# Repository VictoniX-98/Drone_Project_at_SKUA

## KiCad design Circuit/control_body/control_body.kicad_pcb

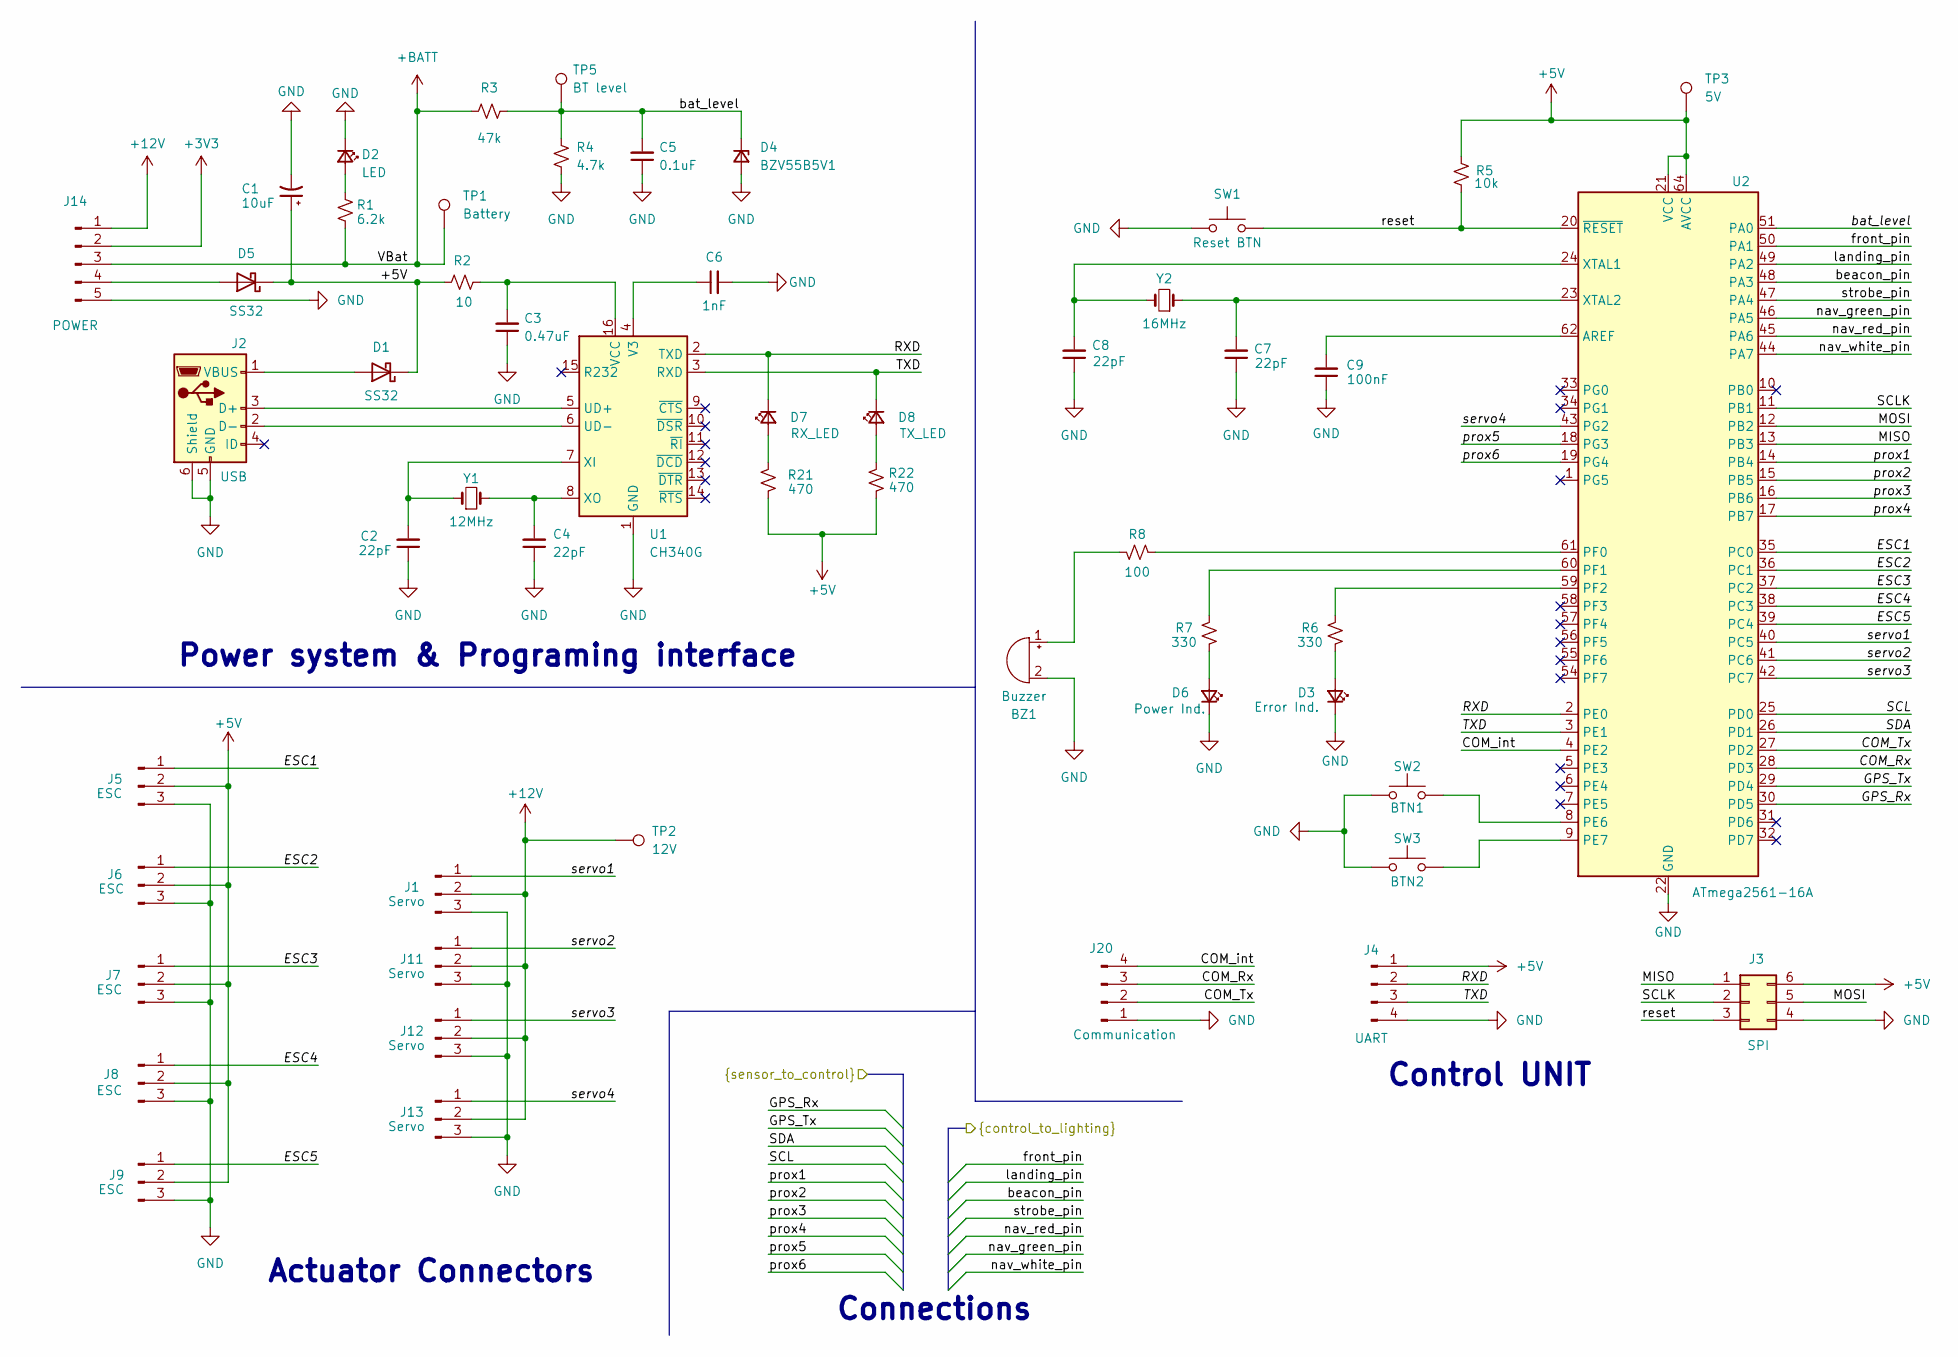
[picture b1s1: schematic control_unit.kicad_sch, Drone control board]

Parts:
BZ1: Buzzer; Buzzer_TDK_PS1240P02BT_D12.2mm_H6.5mm
C1: 10uF; CP_Elec_4x3
C2, C4, C7, C8: 22pF; C_0805_2012Metric_Pad1.18x1.45mm_HandSolder
C3: 0.47uF; C_0805_2012Metric_Pad1.18x1.45mm_HandSolder
C5: 0.1uF; C_0805_2012Metric_Pad1.18x1.45mm_HandSolder
C6: 1nF; C_0805_2012Metric_Pad1.18x1.45mm_HandSolder
C9: 100nF; C_0805_2012Metric_Pad1.18x1.45mm_HandSolder
D1, D5: SS32; D_SMA
D2: LED; LED_1206_3216Metric
D3: Error Ind.; LED_1206_3216Metric
D4: BZV55B5V1; D_MiniMELF
D6: Power Ind.; LED_1206_3216Metric
D7: RX_LED; LED_1206_3216Metric
D8: TX_LED; LED_1206_3216Metric
J1, J11, J12, J13: Servo; Wuerth_WR-WTB_64800311622_1x03_P1.50mm_Vertical
J2: USB; USB_Micro-B_Amphenol_10118194_Horizontal
J3: SPI; PinHeader_2x03_P2.54mm_Vertical
J4: UART; PinHeader_1x04_P2.54mm_Vertical
J5, J6, J7, J8, J9: ESC; Wuerth_WR-WTB_64800311622_1x03_P1.50mm_Vertical
J14: POWER; JST_PH_B5B-PH-K_1x05_P2.00mm_Vertical
J20: Communication; Wuerth_WR-WTB_64800411622_1x04_P1.50mm_Vertical
R1: 6.2k; R_0805_2012Metric_Pad1.20x1.40mm_HandSolder
R2: 10; R_0805_2012Metric_Pad1.20x1.40mm_HandSolder
R3: 47k; R_0805_2012Metric_Pad1.20x1.40mm_HandSolder
R4: 4.7k; R_0805_2012Metric_Pad1.20x1.40mm_HandSolder
R5: 10k; R_0805_2012Metric_Pad1.20x1.40mm_HandSolder
R6, R7: 330; R_0805_2012Metric_Pad1.20x1.40mm_HandSolder
R8: 100; R_0805_2012Metric_Pad1.20x1.40mm_HandSolder
R21, R22: 470; R_0805_2012Metric_Pad1.20x1.40mm_HandSolder
SW1: Reset BTN; SW_SPST_CK_RS282G05A3
SW2: BTN1; SW_SPST_B3U-1000P
SW3: BTN2; SW_SPST_B3U-1000P
TP1: Battery; TestPoint_Pad_D2.0mm
TP2: 12V; TestPoint_Pad_D2.0mm
TP3: 5V; TestPoint_Pad_D2.0mm
TP5: BT level; TestPoint_Pad_D2.0mm
U1: CH340G; SOIC-16_3.9x9.9mm_P1.27mm
U2: ATmega2561-16A; TQFP-64_14x14mm_P0.8mm
Y1: 12MHz; Crystal_SMD_HC49-SD
Y2: 16MHz; Crystal_SMD_HC49-SD

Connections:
+3V3: J14.2; also elsewhere on the board
+5V: BZ1.2 (-), C1.1, C1.2, C2.1, C3.1, C4.1, C5.1, C6.2, C7.1, C8.1, C9.1, D1.1 (K), D2.1 (K), D3.1 (K), D4.2 (A), D5.1 (K), D6.1 (K), J1.3, J2.5 (GND), J2.6 (Shield), J3.4, J3.6, J4.1, J4.4, J5.2, J5.3, J6.2, J6.3, J7.2, J7.3, J8.2, J8.3, J9.2, J9.3, J11.3, J12.3, J13.3, J14.5, J20.1, R2.1, R4.2, R5.1, R21.2, R22.2, SW1.1, SW2.2, SW3.2, TP3.1, U1.1 (GND), U2.21 (VCC), U2.22 (GND), U2.52 (VCC), U2.53 (GND), U2.63 (GND), U2.64 (AVCC); also elsewhere on the board
+12V: J1.2, J11.2, J12.2, J13.2, J14.1, TP2.1; also elsewhere on the board
+BATT: J14.3, R1.2, R3.1, TP1.1; also elsewhere on the board
/Control UNIT/COM_Rx: J20.3, U2.28 (PD3)
/Control UNIT/COM_Tx: J20.2, U2.27 (PD2)
/Control UNIT/COM_int: J20.4, U2.4 (PE2)
/Control UNIT/ESC1: J5.1, U2.35 (PC0)
/Control UNIT/ESC2: J6.1, U2.36 (PC1)
/Control UNIT/ESC3: J7.1, U2.37 (PC2)
/Control UNIT/ESC4: J8.1, U2.38 (PC3)
/Control UNIT/ESC5: J9.1, U2.39 (PC4)
/Control UNIT/GPS_Rx: U2.30 (PD5); also elsewhere on the board
/Control UNIT/GPS_Tx: U2.29 (PD4); also elsewhere on the board
/Control UNIT/MISO: J3.1, U2.13 (PB3)
/Control UNIT/MOSI: J3.5, U2.12 (PB2)
/Control UNIT/RXD: D7.1 (K), J4.2, U1.2 (TXD), U2.2 (PE0)
/Control UNIT/SCL: U2.25 (PD0); also elsewhere on the board
/Control UNIT/SCLK: J3.2, U2.11 (PB1)
/Control UNIT/SDA: U2.26 (PD1); also elsewhere on the board
/Control UNIT/TXD: D8.1 (K), J4.3, U1.3 (RXD), U2.3 (PE1)
/Control UNIT/bat_level: C5.2, D4.1 (K), R3.2, R4.1, TP5.1, U2.51 (PA0)
/Control UNIT/beacon_pin: U2.48 (PA3); also elsewhere on the board
/Control UNIT/front_pin: U2.50 (PA1); also elsewhere on the board
/Control UNIT/landing_pin: U2.49 (PA2); also elsewhere on the board
/Control UNIT/nav_green_pin: U2.46 (PA5); also elsewhere on the board
/Control UNIT/nav_red_pin: U2.45 (PA6); also elsewhere on the board
/Control UNIT/nav_white_pin: U2.44 (PA7); also elsewhere on the board
/Control UNIT/prox1: U2.14 (PB4); also elsewhere on the board
/Control UNIT/prox2: U2.15 (PB5); also elsewhere on the board
/Control UNIT/prox3: U2.16 (PB6); also elsewhere on the board
/Control UNIT/prox4: U2.17 (PB7); also elsewhere on the board
/Control UNIT/prox5: U2.18 (PG3); also elsewhere on the board
/Control UNIT/prox6: U2.19 (PG4); also elsewhere on the board
/Control UNIT/reset: J3.3, R5.2, SW1.2, U2.20 (~RESET)
/Control UNIT/servo1: J1.1, U2.40 (PC5)
/Control UNIT/servo2: J11.1, U2.41 (PC6)
/Control UNIT/servo3: J12.1, U2.42 (PC7)
/Control UNIT/servo4: J13.1, U2.43 (PG2)
/Control UNIT/strobe_pin: U2.47 (PA4); also elsewhere on the board
unnamed: BZ1.1 (+), R8.2
unnamed: D1.2 (A), J2.1 (VBUS)
unnamed: D2.2 (A), R1.1
unnamed: D3.2 (A), R6.1
unnamed: D5.2 (A), J14.4
unnamed: D6.2 (A), R7.1
unnamed: D7.2 (A), R21.1
unnamed: D8.2 (A), R22.1
unnamed: J2.3 (D+), U1.5 (UD+)
unnamed: J2.2 (D-), U1.6 (UD-)
unnamed: C6.1, U1.4 (V3)
unnamed: C3.2, R2.2, U1.16 (VCC)
unnamed: C2.2, U1.7 (XI), Y1.1
unnamed: C4.2, U1.8 (XO), Y1.2
unnamed: C9.2, U2.62 (AREF)
unnamed: SW2.1, U2.8 (PE6)
unnamed: SW3.1, U2.9 (PE7)
unnamed: R8.1, U2.61 (PF0)
unnamed: R7.2, U2.60 (PF1)
unnamed: R6.2, U2.59 (PF2)
unnamed: C8.2, U2.24 (XTAL1), Y2.2
unnamed: C7.2, U2.23 (XTAL2), Y2.1

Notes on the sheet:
Control UNIT
Connections
Power system & Programing interface
Actuator Connectors

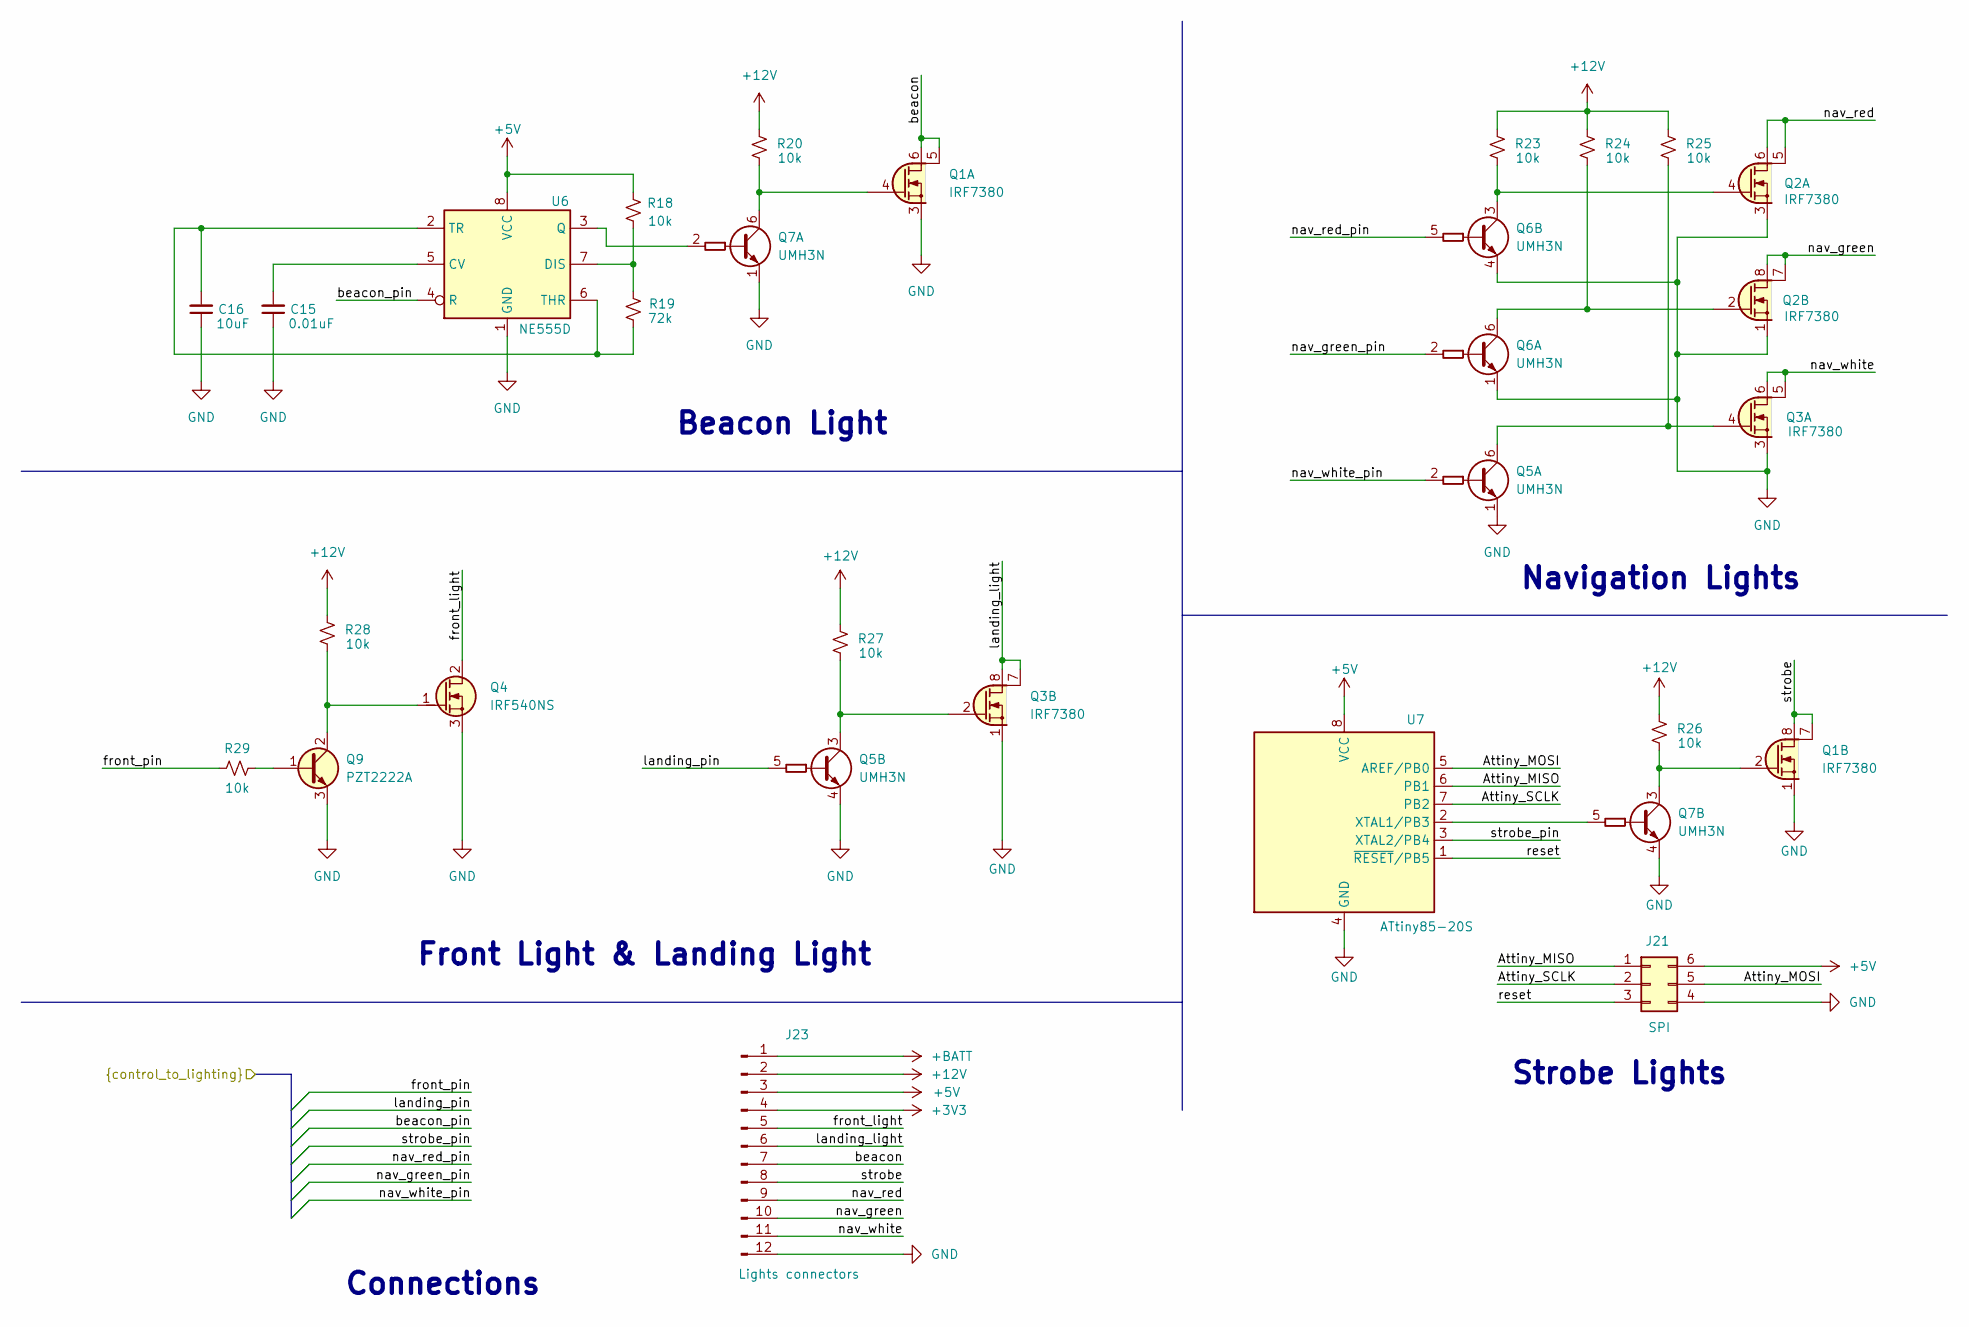
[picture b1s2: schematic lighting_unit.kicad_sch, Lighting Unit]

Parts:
C15: 0.01uF; C_0805_2012Metric_Pad1.18x1.45mm_HandSolder
C16: 10uF; C_0805_2012Metric_Pad1.18x1.45mm_HandSolder
J21: SPI; PinHeader_2x03_P2.54mm_Vertical
J23: Lights connectors; PinHeader_2x06_P2.54mm_Horizontal
Q1, Q2, Q3: IRF7380; SO-8_3.9x4.9mm_P1.27mm
Q4: IRF540NS; TO-263-2
Q5, Q6, Q7: UMH3N; SOT-363_SC-70-6
Q9: PZT2222A; SOT-223-3_TabPin2
R18, R20, R23, R24, R25, R26, R27, R28, R29: 10k; R_0805_2012Metric_Pad1.20x1.40mm_HandSolder
R19: 72k; R_0805_2012Metric_Pad1.20x1.40mm_HandSolder
U6: NE555D; SOIC-8_3.9x4.9mm_P1.27mm
U7: ATtiny85-20S; SOIC-8W_5.3x5.3mm_P1.27mm

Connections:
+3V3: J23.4; also elsewhere on the board
+5V: C15.1, C16.1, J21.4, J21.6, J23.3, J23.12, Q1.1 (S2), Q1.3 (S1), Q2.1 (S2), Q2.3 (S1), Q3.1 (S2), Q3.3 (S1), Q4.3 (S), Q5.1 (E1), Q5.4 (E2), Q6.1 (E1), Q6.4 (E2), Q7.1 (E1), Q7.4 (E2), Q9.3 (E), R18.2, U6.1 (GND), U6.8 (VCC), U7.4 (GND), U7.8 (VCC); also elsewhere on the board
+12V: J23.2, R20.2, R23.2, R24.2, R25.2, R26.2, R27.2, R28.2; also elsewhere on the board
+BATT: J23.1; also elsewhere on the board
/Control UNIT/beacon_pin: U6.4 (R); also elsewhere on the board
/Control UNIT/front_pin: R29.2; also elsewhere on the board
/Control UNIT/landing_pin: Q5.5 (B2); also elsewhere on the board
/Control UNIT/nav_green_pin: Q6.2 (B1); also elsewhere on the board
/Control UNIT/nav_red_pin: Q6.5 (B2); also elsewhere on the board
/Control UNIT/nav_white_pin: Q5.2 (B1); also elsewhere on the board
/Control UNIT/strobe_pin: U7.3 (XTAL2/PB4); also elsewhere on the board
/Lighting UNIT/Attiny_MISO: J21.1, U7.6 (PB1)
/Lighting UNIT/Attiny_MOSI: J21.5, U7.5 (AREF/PB0)
/Lighting UNIT/Attiny_SCLK: J21.2, U7.7 (PB2)
/Lighting UNIT/beacon: J23.7, Q1.5 (D1), Q1.6 (D1)
/Lighting UNIT/front_light: J23.5, Q4.2 (D)
/Lighting UNIT/landing_light: J23.6, Q3.7 (D2), Q3.8 (D2)
/Lighting UNIT/nav_green: J23.10, Q2.7 (D2), Q2.8 (D2)
/Lighting UNIT/nav_red: J23.9, Q2.5 (D1), Q2.6 (D1)
/Lighting UNIT/nav_white: J23.11, Q3.5 (D1), Q3.6 (D1)
/Lighting UNIT/reset: J21.3, U7.1 (~RESET/PB5)
/Lighting UNIT/strobe: J23.8, Q1.7 (D2), Q1.8 (D2)
unnamed: Q1.4 (G1), Q7.6 (C1), R20.1
unnamed: Q1.2 (G2), Q7.3 (C2), R26.1
unnamed: Q2.4 (G1), Q6.3 (C2), R23.1
unnamed: Q2.2 (G2), Q6.6 (C1), R24.1
unnamed: Q3.4 (G1), Q5.6 (C1), R25.1
unnamed: Q3.2 (G2), Q5.3 (C2), R27.1
unnamed: Q4.1 (G), Q9.2 (C), R28.1
unnamed: Q7.2 (B1), U6.3 (Q)
unnamed: Q7.5 (B2), U7.2 (XTAL1/PB3)
unnamed: Q9.1 (B), R29.1
unnamed: C15.2, U6.5 (CV)
unnamed: R18.1, R19.2, U6.7 (DIS)
unnamed: C16.2, R19.1, U6.2 (TR), U6.6 (THR)

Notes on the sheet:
Navigation Lights
Beacon Light
Front Light & Landing Light
Connections
Strobe Lights

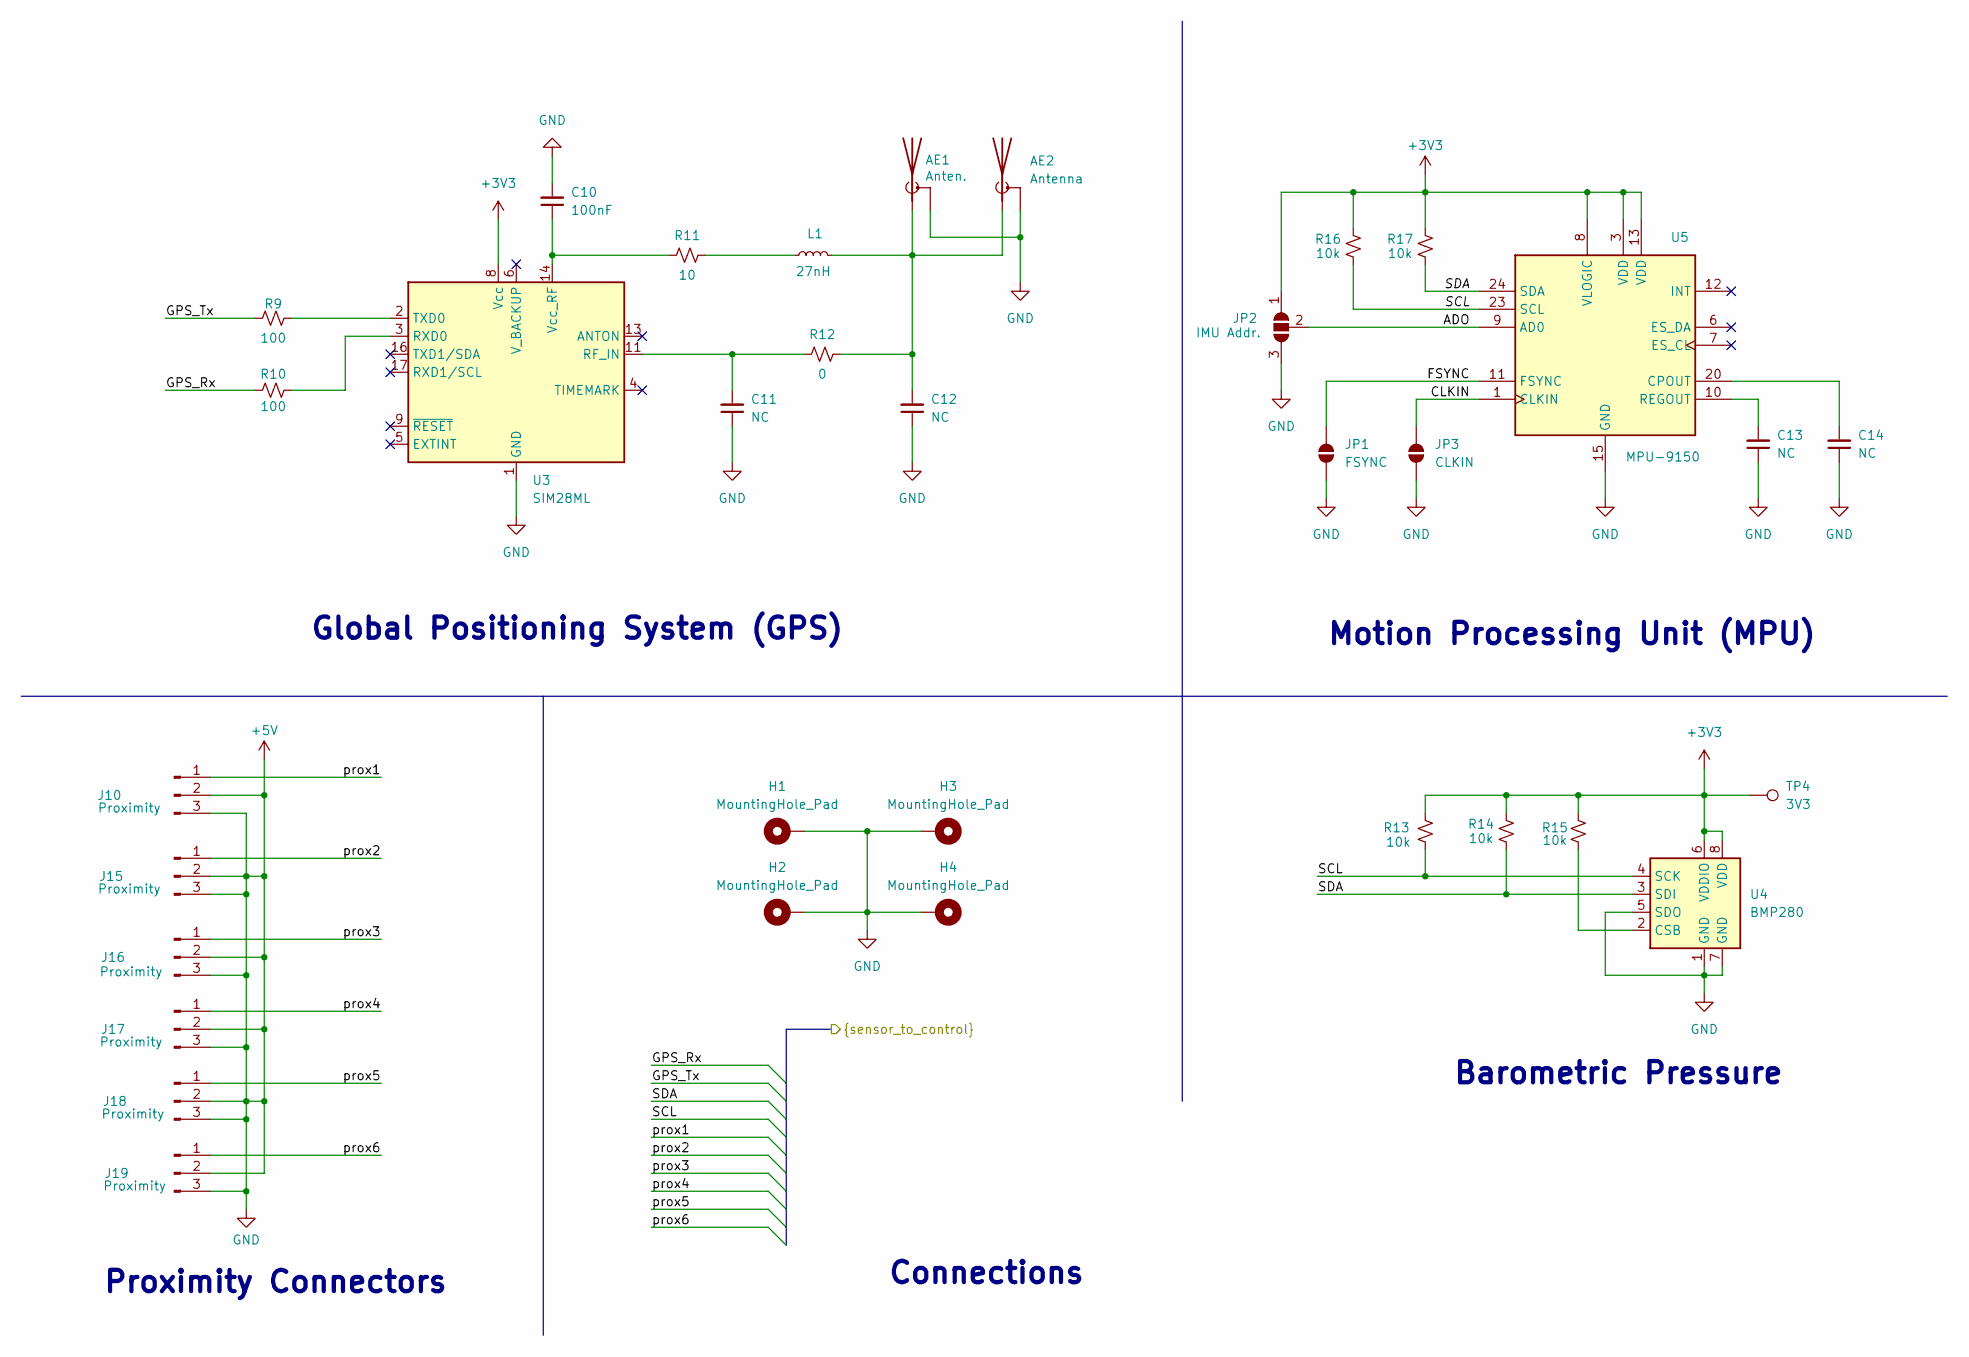
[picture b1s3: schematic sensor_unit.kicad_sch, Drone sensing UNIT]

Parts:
AE1: Anten.; U.FL_Hirose_U.FL-R-SMT-1_Vertical
AE2: Antenna; MMCX_Molex_73415-1471_Vertical
C10: 100nF; C_0805_2012Metric_Pad1.18x1.45mm_HandSolder
C11, C12, C13, C14: NC; C_0805_2012Metric_Pad1.18x1.45mm_HandSolder
H1, H2, H3, H4: MountingHole_Pad; MountingHole_2.2mm_M2_Pad_Via
J10, J15, J16, J17, J18, J19: Proximity; Wuerth_WR-WTB_64800311622_1x03_P1.50mm_Vertical
JP1: FSYNC; SolderJumper-2_P1.3mm_Open_RoundedPad1.0x1.5mm
JP2: IMU Addr.; SolderJumper-3_P1.3mm_Open_RoundedPad1.0x1.5mm
JP3: CLKIN; SolderJumper-2_P1.3mm_Open_RoundedPad1.0x1.5mm
L1: 27nH; L_0805_2012Metric_Pad1.05x1.20mm_HandSolder
R9, R10: 100; R_0805_2012Metric_Pad1.20x1.40mm_HandSolder
R11: 10; R_0805_2012Metric_Pad1.20x1.40mm_HandSolder
R12: 0; R_0805_2012Metric_Pad1.20x1.40mm_HandSolder
R13, R14, R15, R16, R17: 10k; R_0805_2012Metric_Pad1.20x1.40mm_HandSolder
TP4: 3V3; TestPoint_Pad_D2.0mm
U3: SIM28ML
U4: BMP280; Bosch_LGA-8_2x2.5mm_P0.65mm_ClockwisePinNumbering
U5: MPU-9150; InvenSense_QFN-24_4x4mm_P0.5mm

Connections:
+3V3: JP2.1 (A), R13.2, R14.2, R15.2, R16.2, R17.2, TP4.1, U3.8 (Vcc), U4.6 (VDDIO), U4.8 (VDD), U5.3 (VDD), U5.8 (VLOGIC), U5.13 (VDD); also elsewhere on the board
+5V: AE1.2 (Shield), AE2.2 (Shield), C10.2, C11.1, C12.1, C13.1, C14.1, H1.1, H2.1, H3.1, H4.1, J10.2, J10.3, J15.2, J15.3, J16.2, J16.3, J17.2, J17.3, J18.2, J18.3, J19.2, J19.3, JP1.1 (A), JP2.3 (B), JP3.1 (A), U3.1 (GND), U3.10 (GND), U3.12 (GND), U4.1 (GND), U4.5 (SDO), U4.7 (GND), U5.15 (GND), U5.17 (GND), U5.18 (GND); also elsewhere on the board
/Control UNIT/GPS_Rx: R10.1; also elsewhere on the board
/Control UNIT/GPS_Tx: R9.1; also elsewhere on the board
/Control UNIT/SCL: R13.1, R16.1, U4.4 (SCK), U5.23 (SCL); also elsewhere on the board
/Control UNIT/SDA: R14.1, R17.1, U4.3 (SDI), U5.24 (SDA); also elsewhere on the board
/Control UNIT/prox1: J10.1; also elsewhere on the board
/Control UNIT/prox2: J15.1; also elsewhere on the board
/Control UNIT/prox3: J16.1; also elsewhere on the board
/Control UNIT/prox4: J17.1; also elsewhere on the board
/Control UNIT/prox5: J18.1; also elsewhere on the board
/Control UNIT/prox6: J19.1; also elsewhere on the board
/Sensor UNIT/ADO: JP2.2 (C), U5.9 (AD0)
/Sensor UNIT/CLKIN: JP3.2 (B), U5.1 (CLKIN)
/Sensor UNIT/FSYNC: JP1.2 (B), U5.11 (FSYNC)
unnamed: AE1.1 (A), AE2.1 (A), C12.2, L1.2, R12.2
unnamed: L1.1, R11.2
unnamed: C11.2, R12.1, U3.11 (RF_IN)
unnamed: R10.2, U3.3 (RXD0)
unnamed: R9.2, U3.2 (TXD0)
unnamed: C10.1, R11.1, U3.14 (Vcc_RF)
unnamed: R15.1, U4.2 (CSB)
unnamed: C14.2, U5.20 (CPOUT)
unnamed: C13.2, U5.10 (REGOUT)

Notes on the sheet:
Motion Processing Unit (MPU)
Global Positioning System (GPS)
Barometric Pressure
Connections
Proximity Connectors

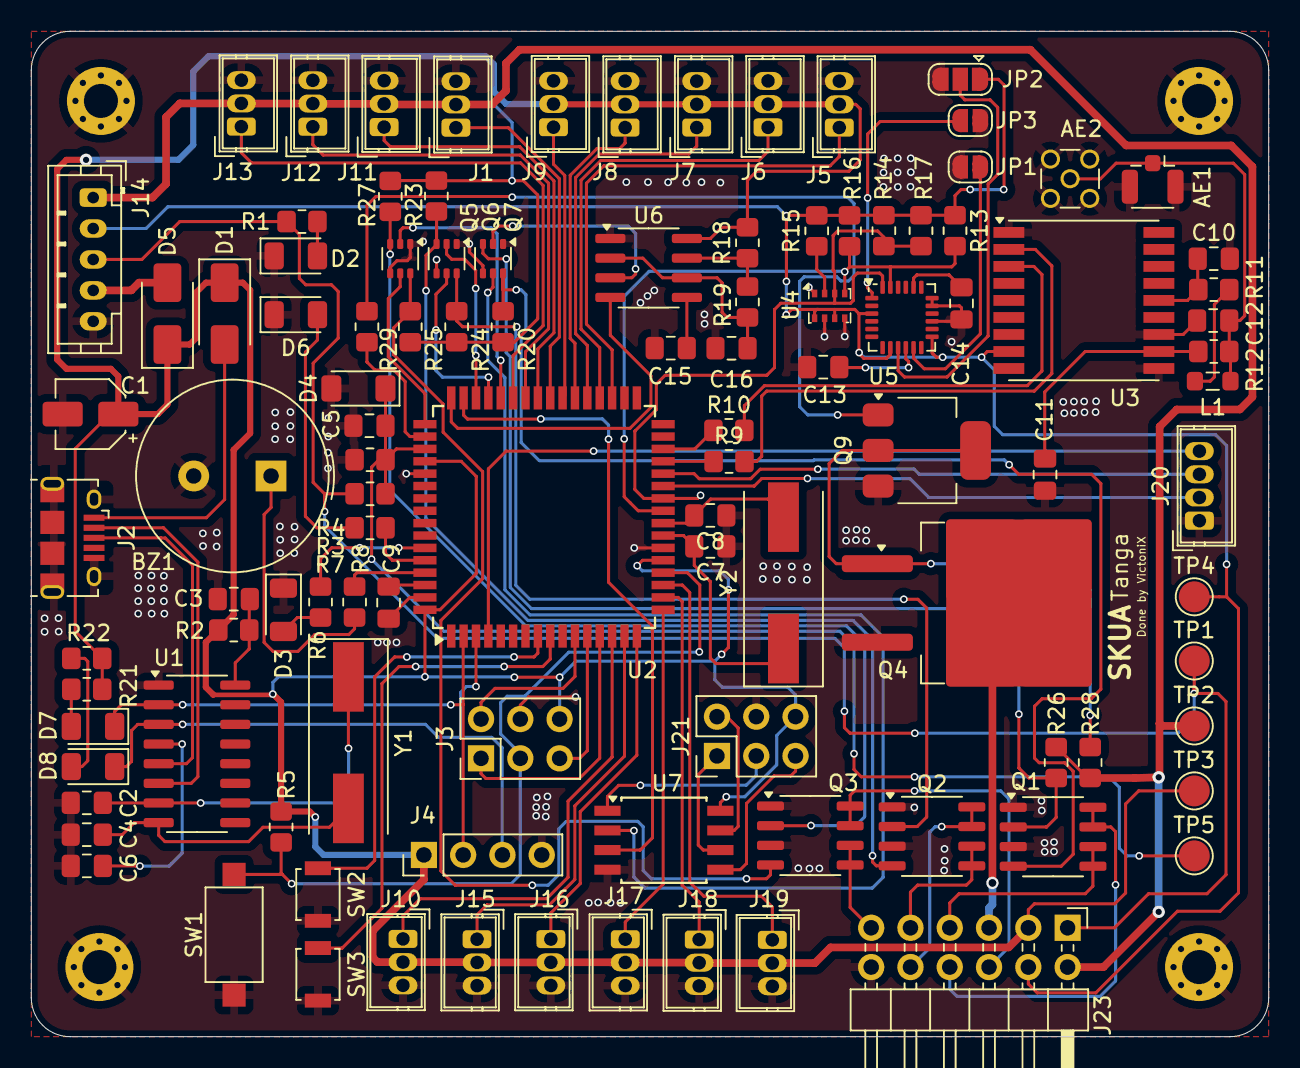
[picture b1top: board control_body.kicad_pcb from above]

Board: 2 copper layers, 80.0 x 65.0 mm, 111 parts (0 on the bottom side), 98 nets.

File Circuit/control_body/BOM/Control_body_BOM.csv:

Designator,Footprint,Comment
AE1,Connector_Coaxial:U.FL_Hirose_U.FL-R-SMT-1_Vertical,Anten.
AE2,Connector_Coaxial:MMCX_Molex_73415-1471_Vertical,Antenna
BZ1,Buzzer_Beeper:Buzzer_TDK_PS1240P02BT_D12.2mm_H6.5mm,Buzzer
"C1,C16",-- mixed values --,10uF
"C2,C4,C7,C8",Capacitor_SMD:C_0805_2012Metric_Pad1.18x1.45mm_HandSolder,22pF
C3,Capacitor_SMD:C_0805_2012Metric_Pad1.18x1.45mm_HandSolder,0.47uF
C5,Capacitor_SMD:C_0805_2012Metric_Pad1.18x1.45mm_HandSolder,0.1uF
C6,Capacitor_SMD:C_0805_2012Metric_Pad1.18x1.45mm_HandSolder,1nF
"C9,C10",Capacitor_SMD:C_0805_2012Metric_Pad1.18x1.45mm_HandSolder,100nF
"C11,C12,C13,C14",Capacitor_SMD:C_0805_2012Metric_Pad1.18x1.45mm_HandSolder,NC
C15,Capacitor_SMD:C_0805_2012Metric_Pad1.18x1.45mm_HandSolder,0.01uF
"D1,D5",Diode_SMD:D_SMA,SS32
D2,LED_SMD:LED_1206_3216Metric,LED
D3,LED_SMD:LED_1206_3216Metric,Error Ind.
D4,Diode_SMD:D_MiniMELF,BZV55B5V1
D6,LED_SMD:LED_1206_3216Metric,Power Ind.
D7,LED_SMD:LED_1206_3216Metric,RX_LED
D8,LED_SMD:LED_1206_3216Metric,TX_LED
"J1,J11,J12,J13",Connector_Wuerth:Wuerth_WR-WTB_64800311622_1x03_P1.50mm_Vertical,Servo
J2,Connector_USB:USB_Micro-B_Molex_47346-0001,USB
"J3,J21",Connector_PinHeader_2.54mm:PinHeader_2x03_P2.54mm_Vertical,SPI
J4,Connector_PinHeader_2.54mm:PinHeader_1x04_P2.54mm_Vertical,UART
"J5,J6,J7,J8,J9",Connector_Wuerth:Wuerth_WR-WTB_64800311622_1x03_P1.50mm_Vertical,ESC
"J10,J15,J16,J17,J18,J19",Connector_Wuerth:Wuerth_WR-WTB_64800311622_1x03_P1.50mm_Vertical,Proximity
J14,Connector_JST:JST_PH_B5B-PH-K_1x05_P2.00mm_Vertical,POWER
J20,Connector_Wuerth:Wuerth_WR-WTB_64800411622_1x04_P1.50mm_Vertical,Communication
J23,Connector_PinHeader_2.54mm:PinHeader_2x06_P2.54mm_Horizontal,Lights connectors
L1,Inductor_SMD:L_0805_2012Metric_Pad1.05x1.20mm_HandSolder,27nH
"Q1,Q2,Q3",Package_SO:SO-8_3.9x4.9mm_P1.27mm,IRF7380
Q4,Package_TO_SOT_SMD:TO-263-2,IRF540NS
"Q5,Q6,Q7",Package_TO_SOT_SMD:SOT-363_SC-70-6,UMH3N
Q9,Package_TO_SOT_SMD:SOT-223-3_TabPin2,PZT2222A
R1,Resistor_SMD:R_0805_2012Metric_Pad1.20x1.40mm_HandSolder,6.2k
R3,Resistor_SMD:R_0805_2012Metric_Pad1.20x1.40mm_HandSolder,47k
R4,Resistor_SMD:R_0805_2012Metric_Pad1.20x1.40mm_HandSolder,4.7k
"R2,R11",Resistor_SMD:R_0805_2012Metric_Pad1.20x1.40mm_HandSolder,10
"R5,R13,R14,R15,R16,R17,R18,R20,R23,R24,R25,R26,R27,R28,R29",Resistor_SMD:R_0805_2012Metric_Pad1.20x1.40mm_HandSolder,10k
"R6,R7",Resistor_SMD:R_0805_2012Metric_Pad1.20x1.40mm_HandSolder,330
"R8,R9,R10",Resistor_SMD:R_0805_2012Metric_Pad1.20x1.40mm_HandSolder,100
R12,Resistor_SMD:R_0805_2012Metric_Pad1.20x1.40mm_HandSolder,0
R19,Resistor_SMD:R_0805_2012Metric_Pad1.20x1.40mm_HandSolder,72k
"R21,R22",Resistor_SMD:R_0805_2012Metric_Pad1.20x1.40mm_HandSolder,470
SW1,Button_Switch_SMD:SW_SPST_CK_RS282G05A3,Reset BTN
SW2,Button_Switch_SMD:SW_SPST_B3U-1000P,BTN1
SW3,Button_Switch_SMD:SW_SPST_B3U-1000P,BTN2
U1,Package_SO:SOIC-16_3.9x9.9mm_P1.27mm,CH340G
U2,Package_QFP:TQFP-64_14x14mm_P0.8mm,ATmega2561-16A
U3,RF_GPS:SIM28ML,SIM28ML
U4,Package_LGA:Bosch_LGA-8_2x2.5mm_P0.65mm_ClockwisePinNumbering,BMP280
U5,Sensor_Motion:InvenSense_QFN-24_4x4mm_P0.5mm,MPU-9150
U6,Package_SO:SOIC-8_3.9x4.9mm_P1.27mm,NE555D
U7,Package_SO:SOIC-8W_5.3x5.3mm_P1.27mm,ATtiny85-20S
Y1,Crystal:Crystal_SMD_HC49-SD,12MHz
Y2,Crystal:Crystal_SMD_HC49-SD,16MHz

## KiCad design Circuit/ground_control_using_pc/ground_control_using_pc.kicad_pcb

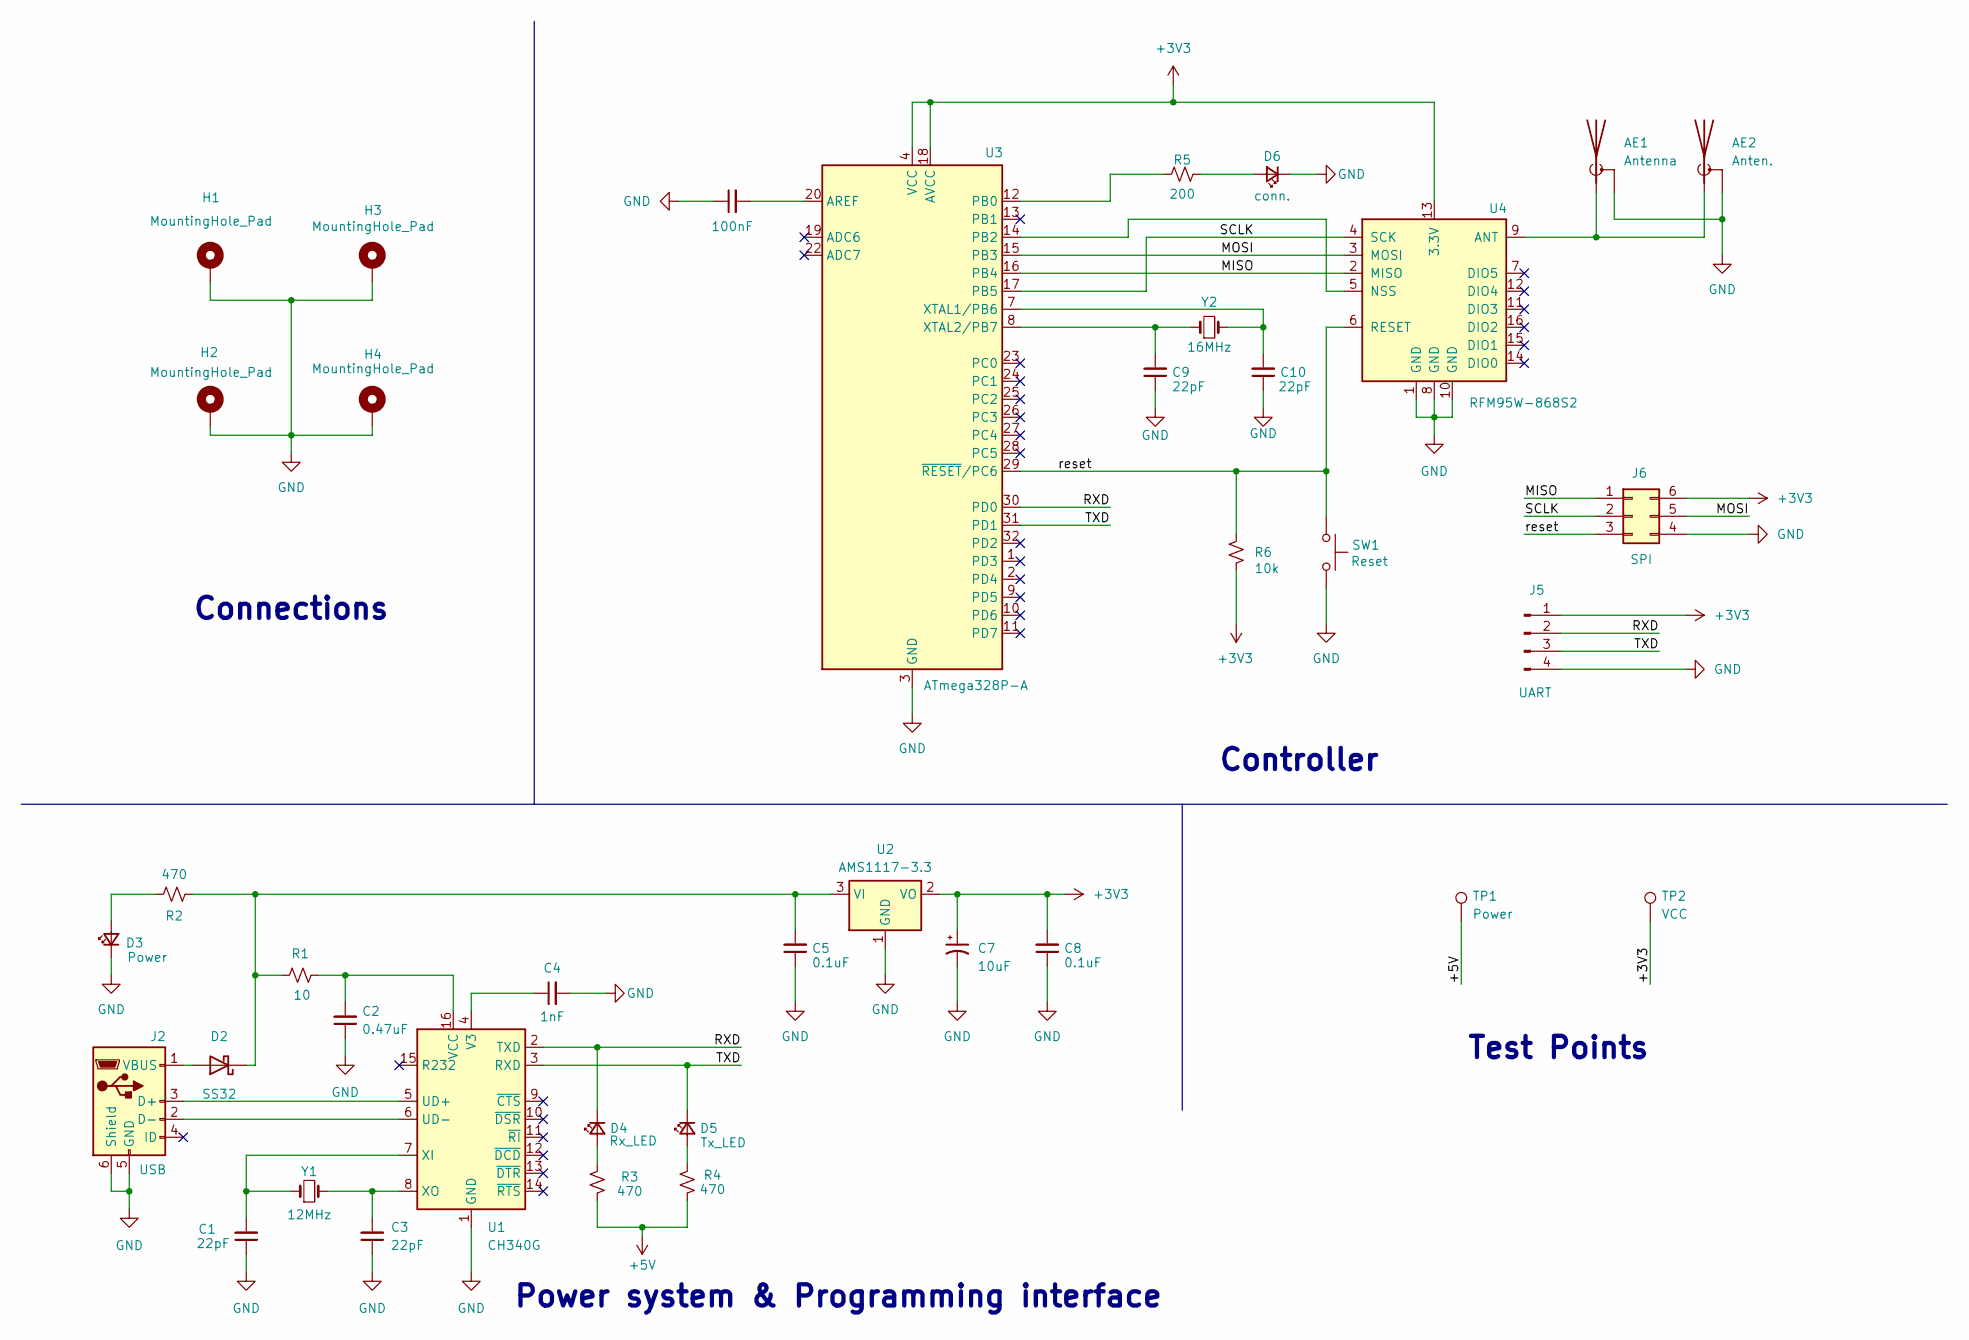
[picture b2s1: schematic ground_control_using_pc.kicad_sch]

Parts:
AE1: Antenna; MMCX_Molex_73415-1471_Vertical
AE2: Anten.; U.FL_Hirose_U.FL-R-SMT-1_Vertical
C1, C3, C9, C10: 22pF; C_0805_2012Metric_Pad1.18x1.45mm_HandSolder
C2: 0.47uF; C_0805_2012Metric_Pad1.18x1.45mm_HandSolder
C4: 1nF; C_0805_2012Metric_Pad1.18x1.45mm_HandSolder
C5, C8: 0.1uF; C_0805_2012Metric_Pad1.18x1.45mm_HandSolder
C6: 100nF; C_0805_2012Metric_Pad1.18x1.45mm_HandSolder
C7: 10uF; C_Elec_4x5.4
D2: SS32; D_SMA
D3: Power; LED_1206_3216Metric
D4: Rx_LED; LED_1206_3216Metric
D5: Tx_LED; LED_1206_3216Metric
D6: conn.; LED_1206_3216Metric
H1, H2, H3, H4: MountingHole_Pad; MountingHole_2.2mm_M2_DIN965_Pad
J2: USB; USB_Micro-B_Amphenol_10118194_Horizontal
J5: UART; PinHeader_1x04_P2.54mm_Vertical
J6: SPI; PinHeader_2x03_P2.54mm_Vertical
R1: 10; R_0805_2012Metric_Pad1.20x1.40mm_HandSolder
R2, R3, R4: 470; R_0805_2012Metric_Pad1.20x1.40mm_HandSolder
R5: 200; R_0805_2012Metric_Pad1.20x1.40mm_HandSolder
R6: 10k; R_0805_2012Metric_Pad1.20x1.40mm_HandSolder
SW1: Reset; SW_SPST_CK_RS282G05A3
TP1: Power; TestPoint_Pad_D1.0mm
TP2: VCC; TestPoint_Pad_D1.0mm
U1: CH340G; SOIC-16_3.9x9.9mm_P1.27mm
U2: AMS1117-3.3; SOT-223-3_TabPin2
U3: ATmega328P-A; TQFP-32_7x7mm_P0.8mm
U4: RFM95W-868S2; HOPERF_RFM9XW_SMD
Y1: 12MHz; Crystal_SMD_HC49-SD
Y2: 16MHz; Crystal_SMD_HC49-SD

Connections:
+3V3: C7.1, C8.2, J5.1, J6.6, R6.1, TP2.1, U2.2 (VO), U3.4 (VCC), U3.6 (VCC), U3.18 (AVCC), U4.13 (3.3V)
+5V: R3.2, R4.2, TP1.1
/MISO: J6.1, U3.16 (PB4), U4.2 (MISO)
/MOSI: J6.5, U3.15 (PB3), U4.3 (MOSI)
/RXD: D4.1 (K), J5.2, U1.2 (TXD), U3.30 (PD0)
/SCLK: J6.2, U3.17 (PB5), U4.4 (SCK)
/TXD: D5.1 (K), J5.3, U1.3 (RXD), U3.31 (PD1)
/reset: J6.3, R6.2, SW1.2, U3.29 (~RESET/PC6), U4.6 (RESET)
GND: AE1.2 (Shield), AE2.2 (Shield), C1.1, C2.1, C3.1, C4.2, C5.1, C6.1, C7.2, C8.1, C9.1, C10.1, D3.1 (K), D6.1 (K), H1.1, H2.1, H3.1, H4.1, J2.5 (GND), J2.6 (Shield), J5.4, J6.4, SW1.1, U1.1 (GND), U2.1 (GND), U3.3 (GND), U3.5 (GND), U3.21 (GND), U4.1 (GND), U4.8 (GND), U4.10 (GND)
unnamed: AE1.1 (A), AE2.1 (A), U4.9 (ANT)
unnamed: D2.2 (A), J2.1 (VBUS)
unnamed: C5.2, D2.1 (K), R1.1, R2.2, U2.3 (VI)
unnamed: D3.2 (A), R2.1
unnamed: D4.2 (A), R3.1
unnamed: D5.2 (A), R4.1
unnamed: D6.2 (A), R5.1
unnamed: J2.3 (D+), U1.5 (UD+)
unnamed: J2.2 (D-), U1.6 (UD-)
unnamed: C4.1, U1.4 (V3)
unnamed: C2.2, R1.2, U1.16 (VCC)
unnamed: C1.2, U1.7 (XI), Y1.1
unnamed: C3.2, U1.8 (XO), Y1.2
unnamed: C6.2, U3.20 (AREF)
unnamed: R5.2, U3.12 (PB0)
unnamed: U3.14 (PB2), U4.5 (NSS)
unnamed: C10.2, U3.7 (XTAL1/PB6), Y2.2
unnamed: C9.2, U3.8 (XTAL2/PB7), Y2.1

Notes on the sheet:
Controller
Power system & Programming interface
Test Points
Connections

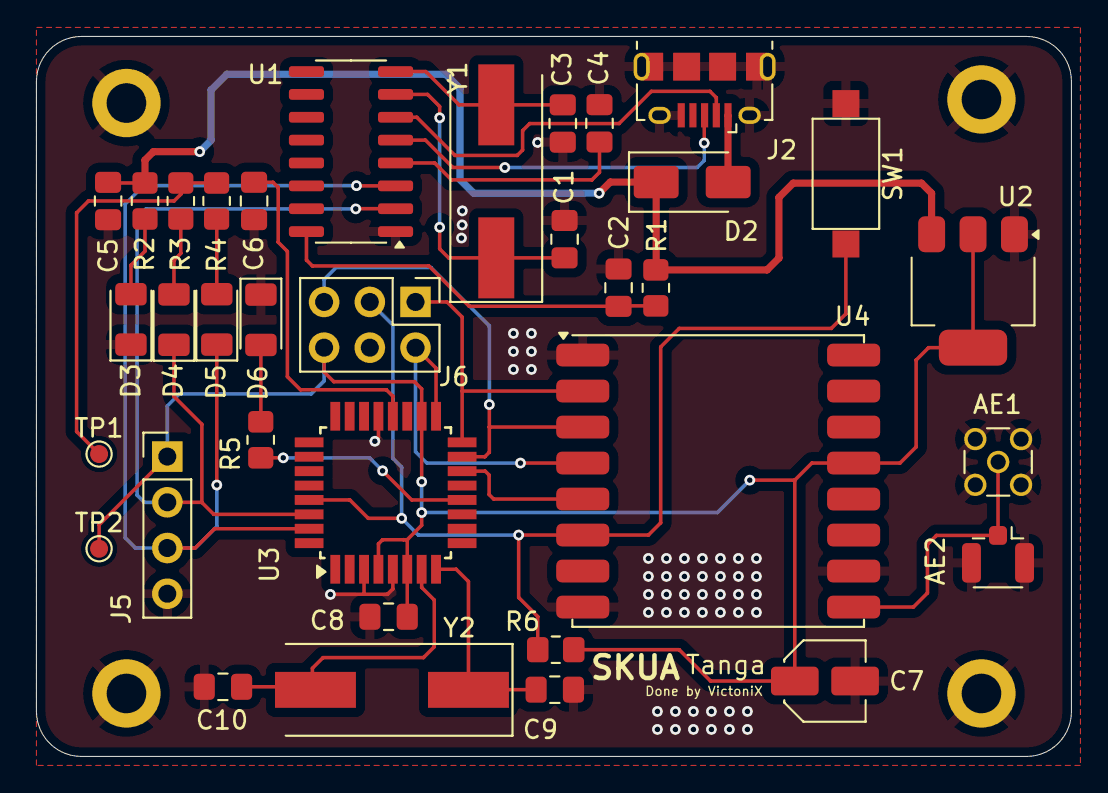
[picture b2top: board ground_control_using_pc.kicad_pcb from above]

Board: 2 copper layers, 57.5 x 40.0 mm, 39 parts (0 on the bottom side), 27 nets.
